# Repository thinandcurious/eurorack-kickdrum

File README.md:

# eurorack-kickdrum

Design based on Moritz Klein: https://www.youtube.com/watch?v=yz37Yz315eU

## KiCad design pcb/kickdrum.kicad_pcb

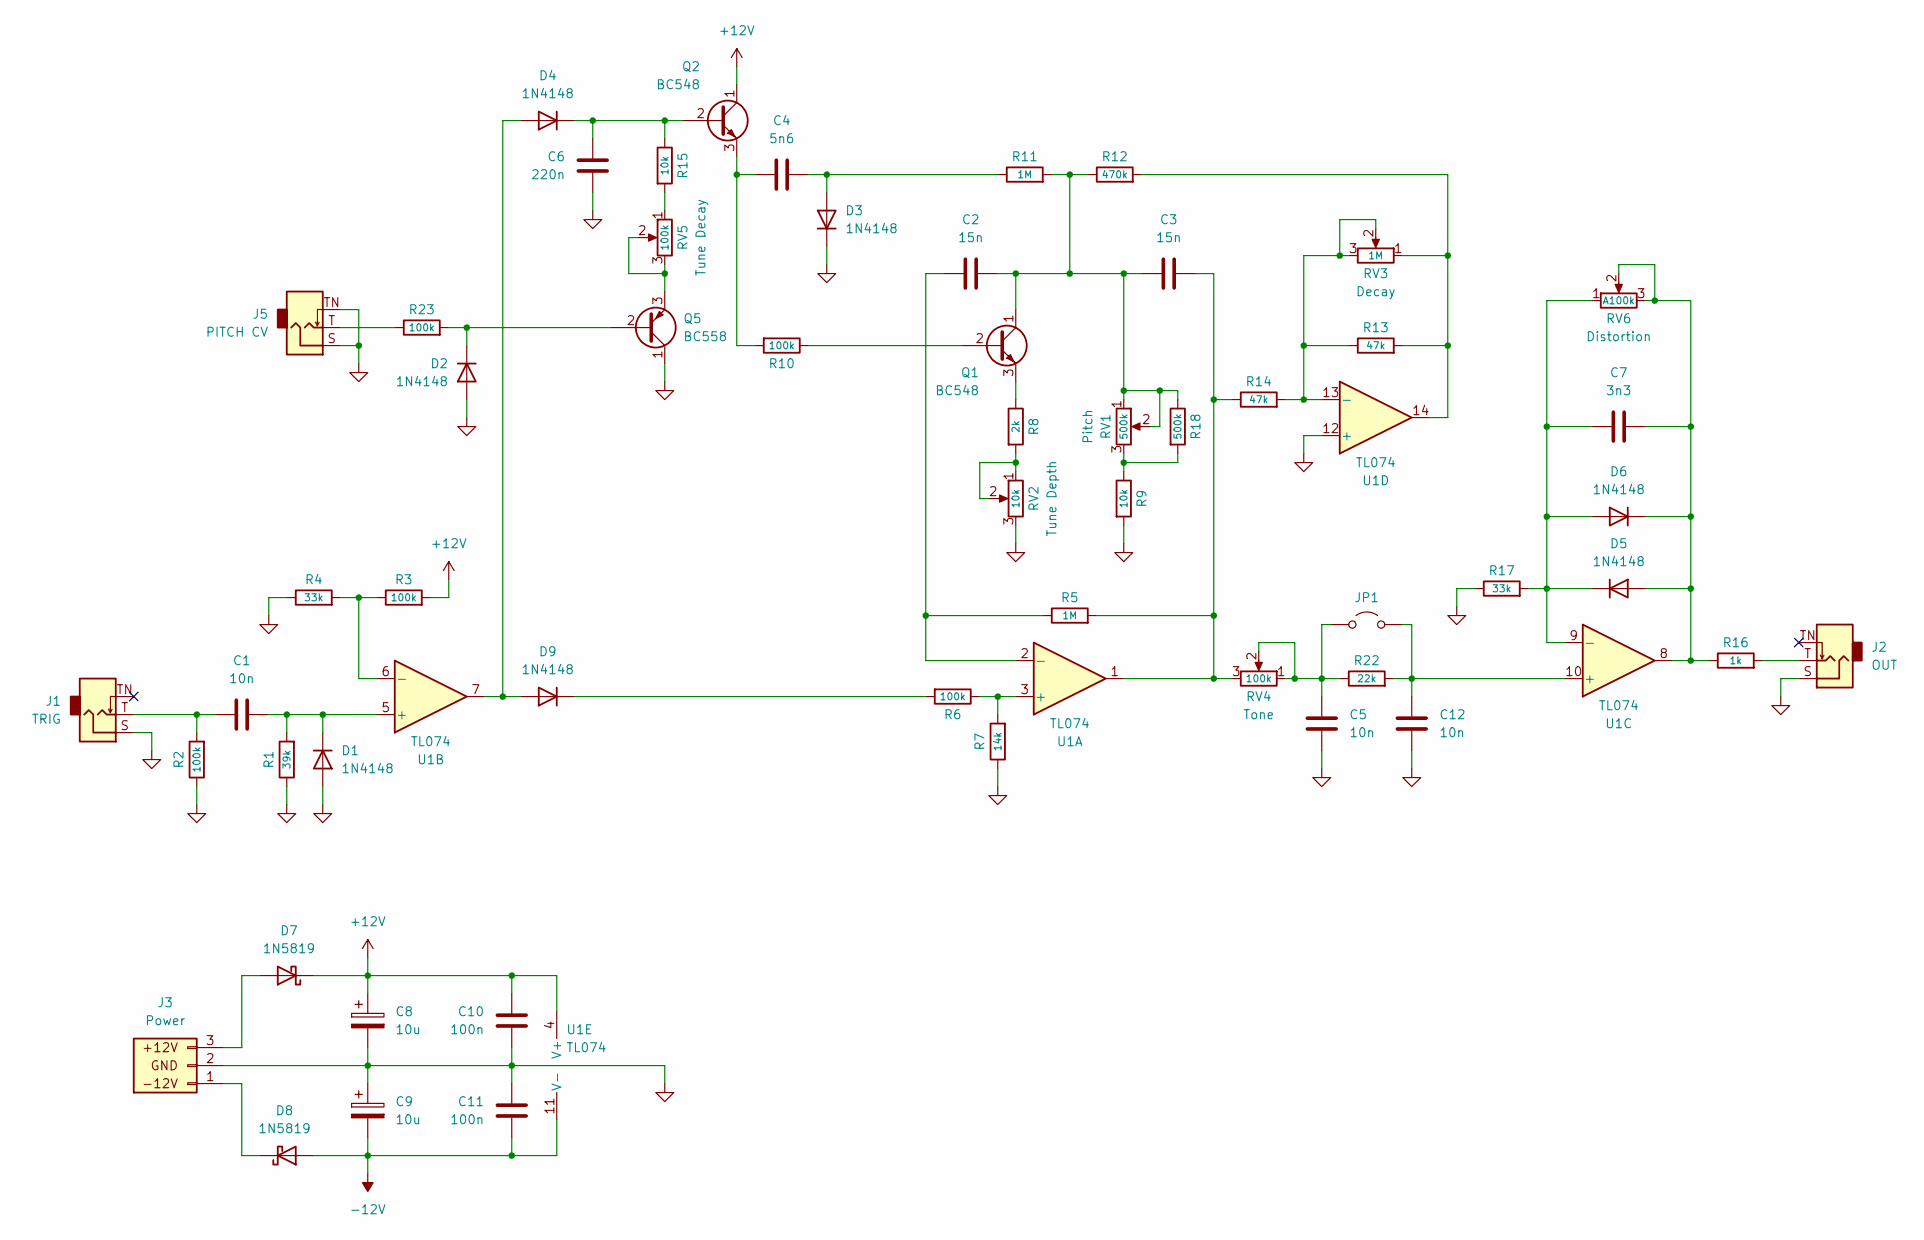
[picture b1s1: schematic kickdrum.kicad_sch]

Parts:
C1, C5, C12: 10n; C_Rect_L7.2mm_W3.5mm_P5.00mm_FKS2_FKP2_MKS2_MKP2
C2, C3: 15n; C_Rect_L4.6mm_W2.0mm_P2.50mm_MKS02_FKP02
C4: 5n6; C_Rect_L9.0mm_W4.2mm_P7.50mm_MKT
C6: 220n; C_Rect_L7.2mm_W3.5mm_P5.00mm_FKS2_FKP2_MKS2_MKP2
C7: 3n3; C_Rect_L7.2mm_W3.5mm_P5.00mm_FKS2_FKP2_MKS2_MKP2
C8, C9: 10u; CP_Radial_D6.3mm_P2.50mm
C10, C11: 100n; C_0805_HandSolder
D1, D2, D3, D4, D5, D6, D9: 1N4148; D_DO-35_SOD27_P5.08mm_Horizontal
D7, D8: 1N5819; D_DO-41_SOD81_P7.62mm_Horizontal
J1: TRIG; Jack_3.5mm_PJ398SM_Vertical
J2: OUT; Jack_3.5mm_PJ398SM_Vertical
J3: Power; JST_XH_B3B-XH-A_1x03_P2.50mm_Vertical
J5: PITCH CV; Jack_3.5mm_PJ398SM_Vertical
JP1: Jumper_2_Open; SolderJumper-2_P1.3mm_Open_TrianglePad1.0x1.5mm
Q1, Q2: BC548; TO-92_Inline_Wide
Q5: BC558; TO-92_Inline_Wide
R1: 39k; R_Axial_DIN0207_L6.3mm_D2.5mm_P7.62mm_Horizontal
R2, R3, R6, R10, R23: 100k; R_Axial_DIN0207_L6.3mm_D2.5mm_P7.62mm_Horizontal
R4, R17: 33k; R_Axial_DIN0207_L6.3mm_D2.5mm_P7.62mm_Horizontal
R5, R11: 1M; R_Axial_DIN0207_L6.3mm_D2.5mm_P7.62mm_Horizontal
R7: 14k; R_Axial_DIN0207_L6.3mm_D2.5mm_P7.62mm_Horizontal
R8: 2k; R_Axial_DIN0207_L6.3mm_D2.5mm_P7.62mm_Horizontal
R9, R15: 10k; R_Axial_DIN0207_L6.3mm_D2.5mm_P7.62mm_Horizontal
R12: 470k; R_Axial_DIN0207_L6.3mm_D2.5mm_P7.62mm_Horizontal
R13, R14: 47k; R_Axial_DIN0207_L6.3mm_D2.5mm_P7.62mm_Horizontal
R16: 1k; R_Axial_DIN0207_L6.3mm_D2.5mm_P7.62mm_Horizontal
R18: 500k; R_Axial_DIN0207_L6.3mm_D2.5mm_P7.62mm_Horizontal
R22: 22k; R_Axial_DIN0207_L6.3mm_D2.5mm_P7.62mm_Horizontal
RV1: 500k; Potentiometer_Alpha_RD901F
RV2: 10k; Potentiometer_Alpha_RD901F
RV3: 1M; Potentiometer_Alpha_RD901F
RV4, RV5: 100k; Potentiometer_Alpha_RD901F
RV6: A100k; Potentiometer_Alpha_RD901F
U1: TL074; DIP-14_W7.62mm

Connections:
+12V: C8.1, C10.2, D7.1 (K), Q2.1 (C), R3.2, U1.4 (V+)
-12V: C9.2, C11.1, D8.2 (A), U1.11 (V-)
GND: C5.2, C6.2, C8.2, C9.1, C10.1, C11.2, C12.2, D1.2 (A), D2.2 (A), D3.1 (K), J1.S, J2.S, J3.2, J5.S, J5.TN, Q5.1 (C), R1.1, R2.1, R4.1, R7.1, R9.2, R17.1, RV2.3, U1.12 (+)
unnamed: C1.1, J1.T, R2.2
unnamed: C3.2, R5.2, R14.1, RV4.3, U1.1
unnamed: C1.2, D1.1 (K), R1.2, U1.5 (+)
unnamed: D2.1 (K), Q5.2 (B), R23.2
unnamed: C4.2, D3.2 (A), R11.1
unnamed: D4.2 (A), D9.2 (A), U1.7
unnamed: C6.1, D4.1 (K), Q2.2 (B), R15.1
unnamed: C7.2, D5.2 (A), D6.1 (K), R16.1, RV6.2, RV6.3, U1.8
unnamed: C7.1, D5.1 (K), D6.2 (A), R17.2, RV6.1, U1.9 (-)
unnamed: D7.2 (A), J3.3
unnamed: D8.1 (K), J3.1
unnamed: D9.1 (K), R6.2
unnamed: J2.T, R16.2
unnamed: J5.T, R23.1
unnamed: C5.1, JP1.1 (A), R22.1, RV4.1, RV4.2
unnamed: C12.1, JP1.2 (B), R22.2, U1.10 (+)
unnamed: Q1.2 (B), R10.1
unnamed: C2.2, C3.1, Q1.1 (C), R11.2, R12.1, R18.1, RV1.1, RV1.2
unnamed: Q1.3 (E), R8.1
unnamed: C4.1, Q2.3 (E), R10.2
unnamed: Q5.3 (E), RV5.2, RV5.3
unnamed: R8.2, RV2.1, RV2.2
unnamed: R9.1, R18.2, RV1.3
unnamed: R12.2, R13.2, RV3.1, U1.14
unnamed: R15.2, RV5.1
unnamed: R6.1, R7.2, U1.3 (+)
unnamed: C2.1, R5.1, U1.2 (-)
unnamed: R3.1, R4.2, U1.6 (-)
unnamed: R13.1, R14.2, RV3.2, RV3.3, U1.13 (-)

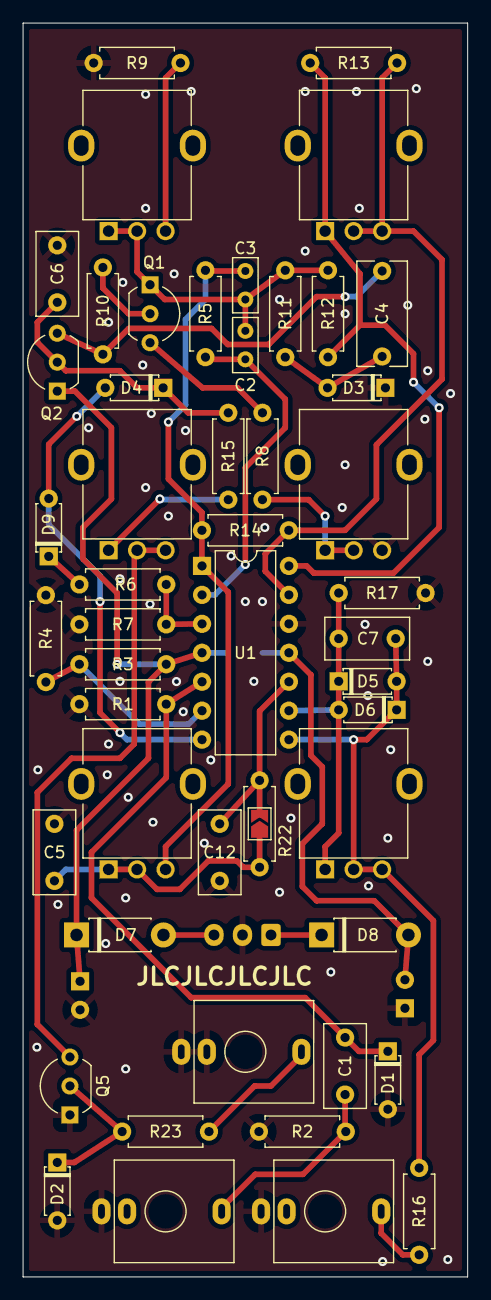
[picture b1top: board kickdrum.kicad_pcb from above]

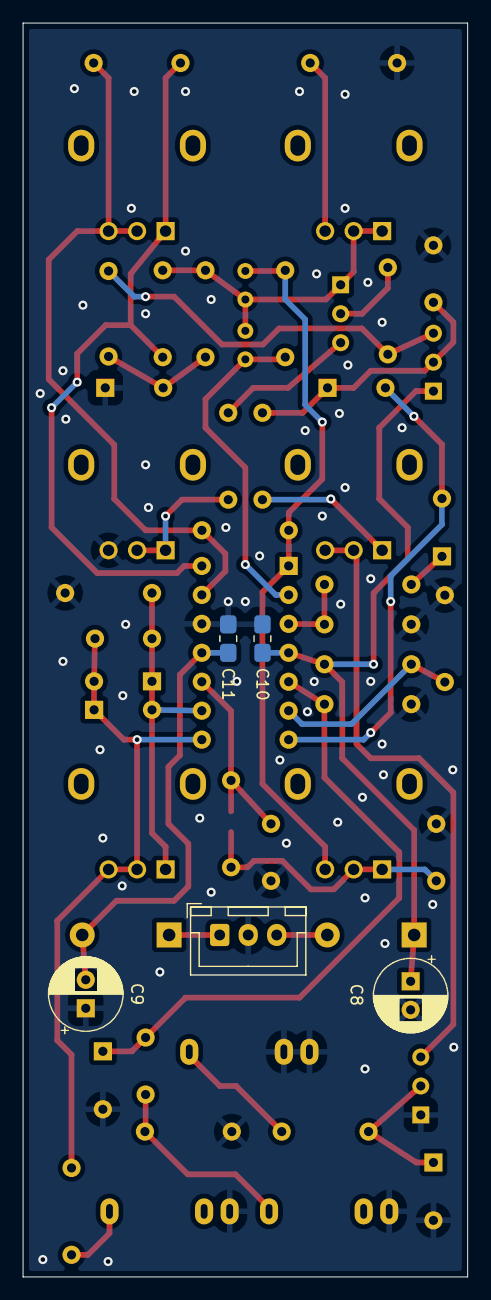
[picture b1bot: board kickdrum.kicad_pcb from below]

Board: 2 copper layers, 39.0 x 110.0 mm, 55 parts (5 on the bottom side), 32 nets.

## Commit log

2025-03-17 upload
